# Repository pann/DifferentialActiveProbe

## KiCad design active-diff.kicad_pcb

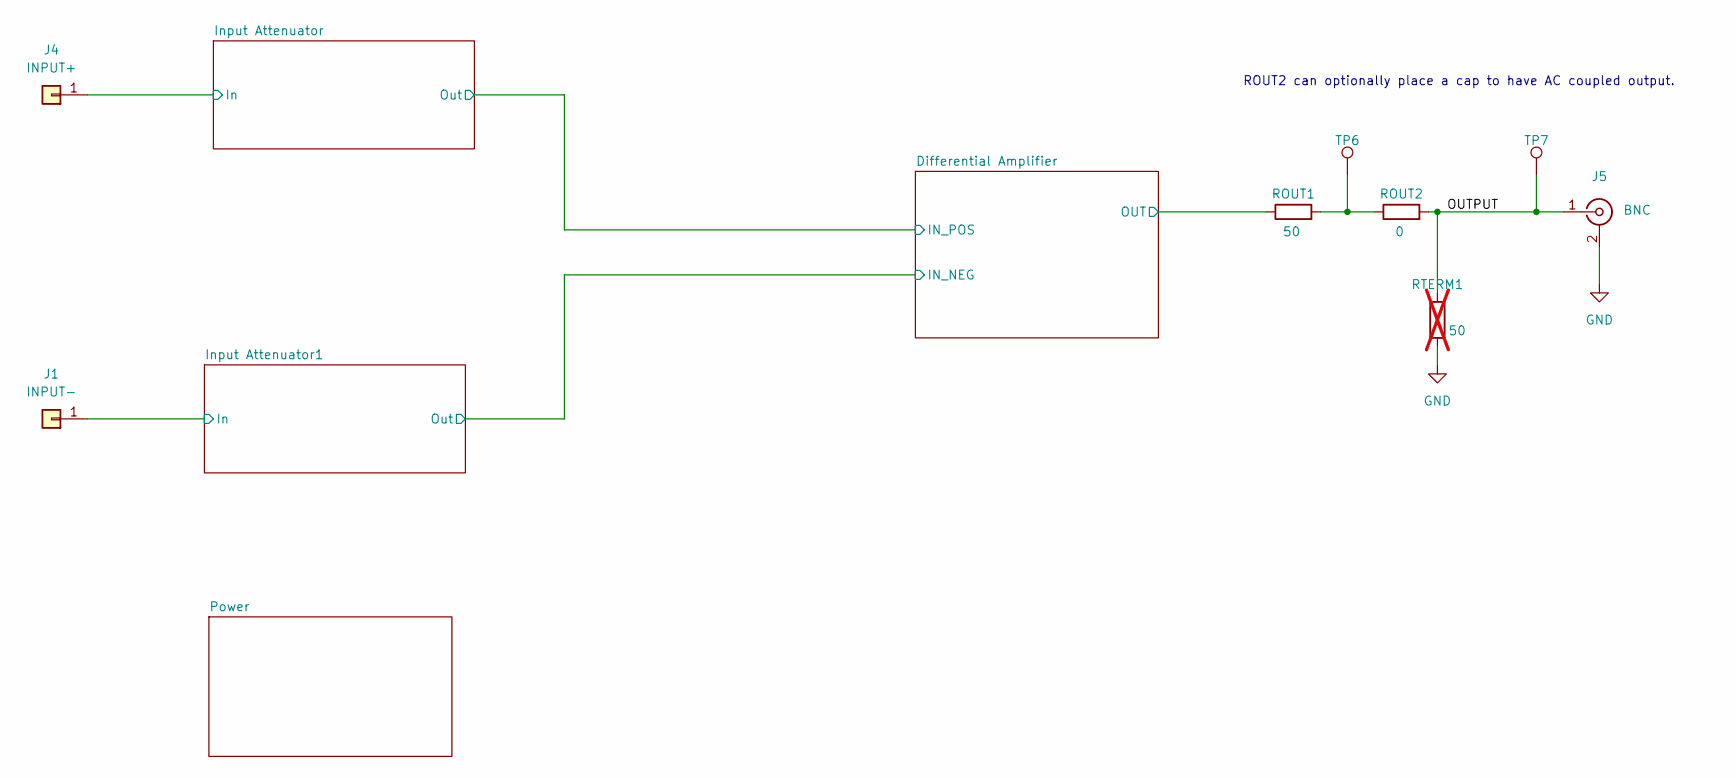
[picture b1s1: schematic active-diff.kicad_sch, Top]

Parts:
J1: INPUT-; TestPoint_Pad_2.5x2.5mm
J4: INPUT+; TestPoint_Pad_2.5x2.5mm
J5: BNC; BNC_Amphenol_B6252HB-NPP3G-50_Horizontal
ROUT1: 50; R_0402_1005Metric_Pad0.72x0.64mm_HandSolder; JLCPCB# C227387
ROUT2: 0; R_0402_1005Metric_Pad0.72x0.64mm_HandSolder; JLCPCB# C17168
RTERM1: 50; R_0402_1005Metric_Pad0.72x0.64mm_HandSolder; not fitted
TP6, TP7: TP; TestPoint_Pad_D1.0mm

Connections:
/Differential Amplifier/OUT: ROUT1.1; also elsewhere on the board
/Input Attenuator1/In: J1.1; also elsewhere on the board
/Input Attenuator/In: J4.1; also elsewhere on the board
/OUTPUT: J5.1 (In), ROUT2.2, RTERM1.1, TP7.1
GND: J5.2 (Ext), RTERM1.2; also elsewhere on the board
unnamed: ROUT1.2, ROUT2.1, TP6.1

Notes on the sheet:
ROUT2 can optionally place a cap to have AC coupled output.

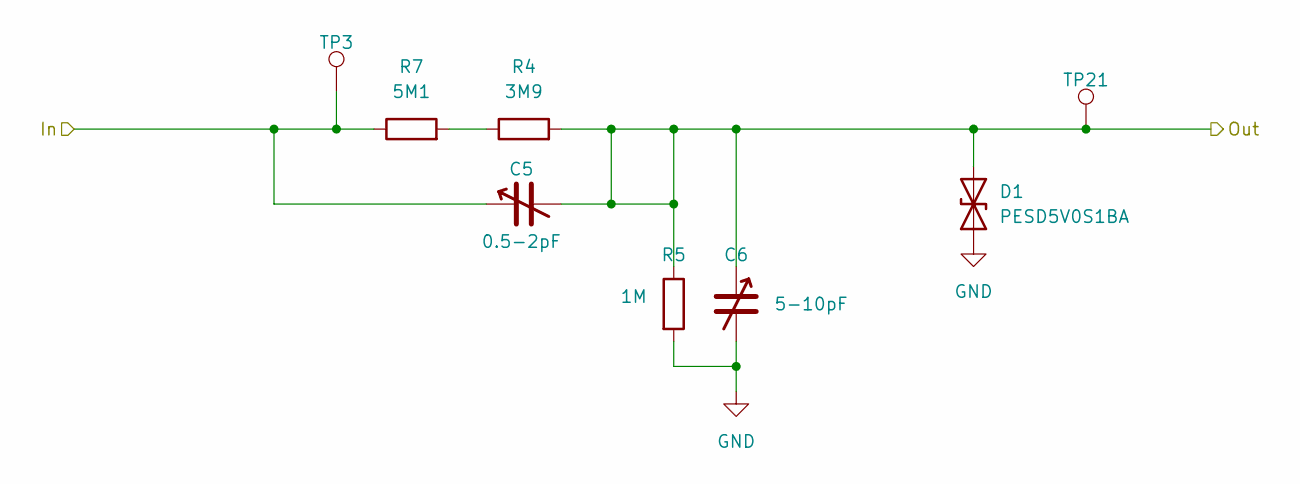
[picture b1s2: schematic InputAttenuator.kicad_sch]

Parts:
C5: 0.5-2pF; C_Trimmer_Murata_TZC3; JLCPCB# C22468120
C6: 5-10pF; C_Trimmer_Murata_TZC3; JLCPCB# C22468120
D1: PESD5V0S1BA; D_SOD-323_HandSoldering; JLCPCB# C2827694
R4: 3M9; R_0603_1608Metric_Pad0.98x0.95mm_HandSolder; Tolerance 0.1%; JLCPCB# C423039
R5: 1M; R_0603_1608Metric_Pad0.98x0.95mm_HandSolder; Tolerance 0.1%; JLCPCB# C4165581
R7: 5M1; R_0603_1608Metric_Pad0.98x0.95mm_HandSolder; Tolerance 0.1%; JLCPCB# C13320
TP3, TP21: TP; TestPoint_Pad_D1.0mm

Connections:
/Differential Amplifier/IN_POS: C5.2, C6.1, D1.2 (A2), R4.2, R5.1, TP21.1; also elsewhere on the board
/Input Attenuator/In: C5.1, R7.1, TP3.1; also elsewhere on the board
GND: C6.2, D1.1 (A1), R5.2; also elsewhere on the board
unnamed: R4.1, R7.2

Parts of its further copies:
C1: 0.5-2pF; C_Trimmer_Murata_TZC3; JLCPCB# C22468120
C2: 5-10pF; C_Trimmer_Murata_TZC3; JLCPCB# C22468120
D2: PESD5V0S1BA; D_SOD-323_HandSoldering; JLCPCB# C2827694
R1: 3M9; R_0603_1608Metric_Pad0.98x0.95mm_HandSolder; Tolerance 0.1%; JLCPCB# C423039
R2: 1M; R_0603_1608Metric_Pad0.98x0.95mm_HandSolder; Tolerance 0.1%; JLCPCB# C4165581
R16: 5M1; R_0603_1608Metric_Pad0.98x0.95mm_HandSolder; Tolerance 0.1%; JLCPCB# C13320
TP1, TP22: TP; TestPoint_Pad_D1.0mm

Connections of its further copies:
/Differential Amplifier/IN_NEG: C1.2, C2.1, D2.2 (A2), R1.2, R2.1, TP22.1; also elsewhere on the board
/Input Attenuator1/In: C1.1, R16.1, TP1.1; also elsewhere on the board
GND: C2.2, D2.1 (A1), R2.2; also elsewhere on the board
unnamed: R1.1, R16.2

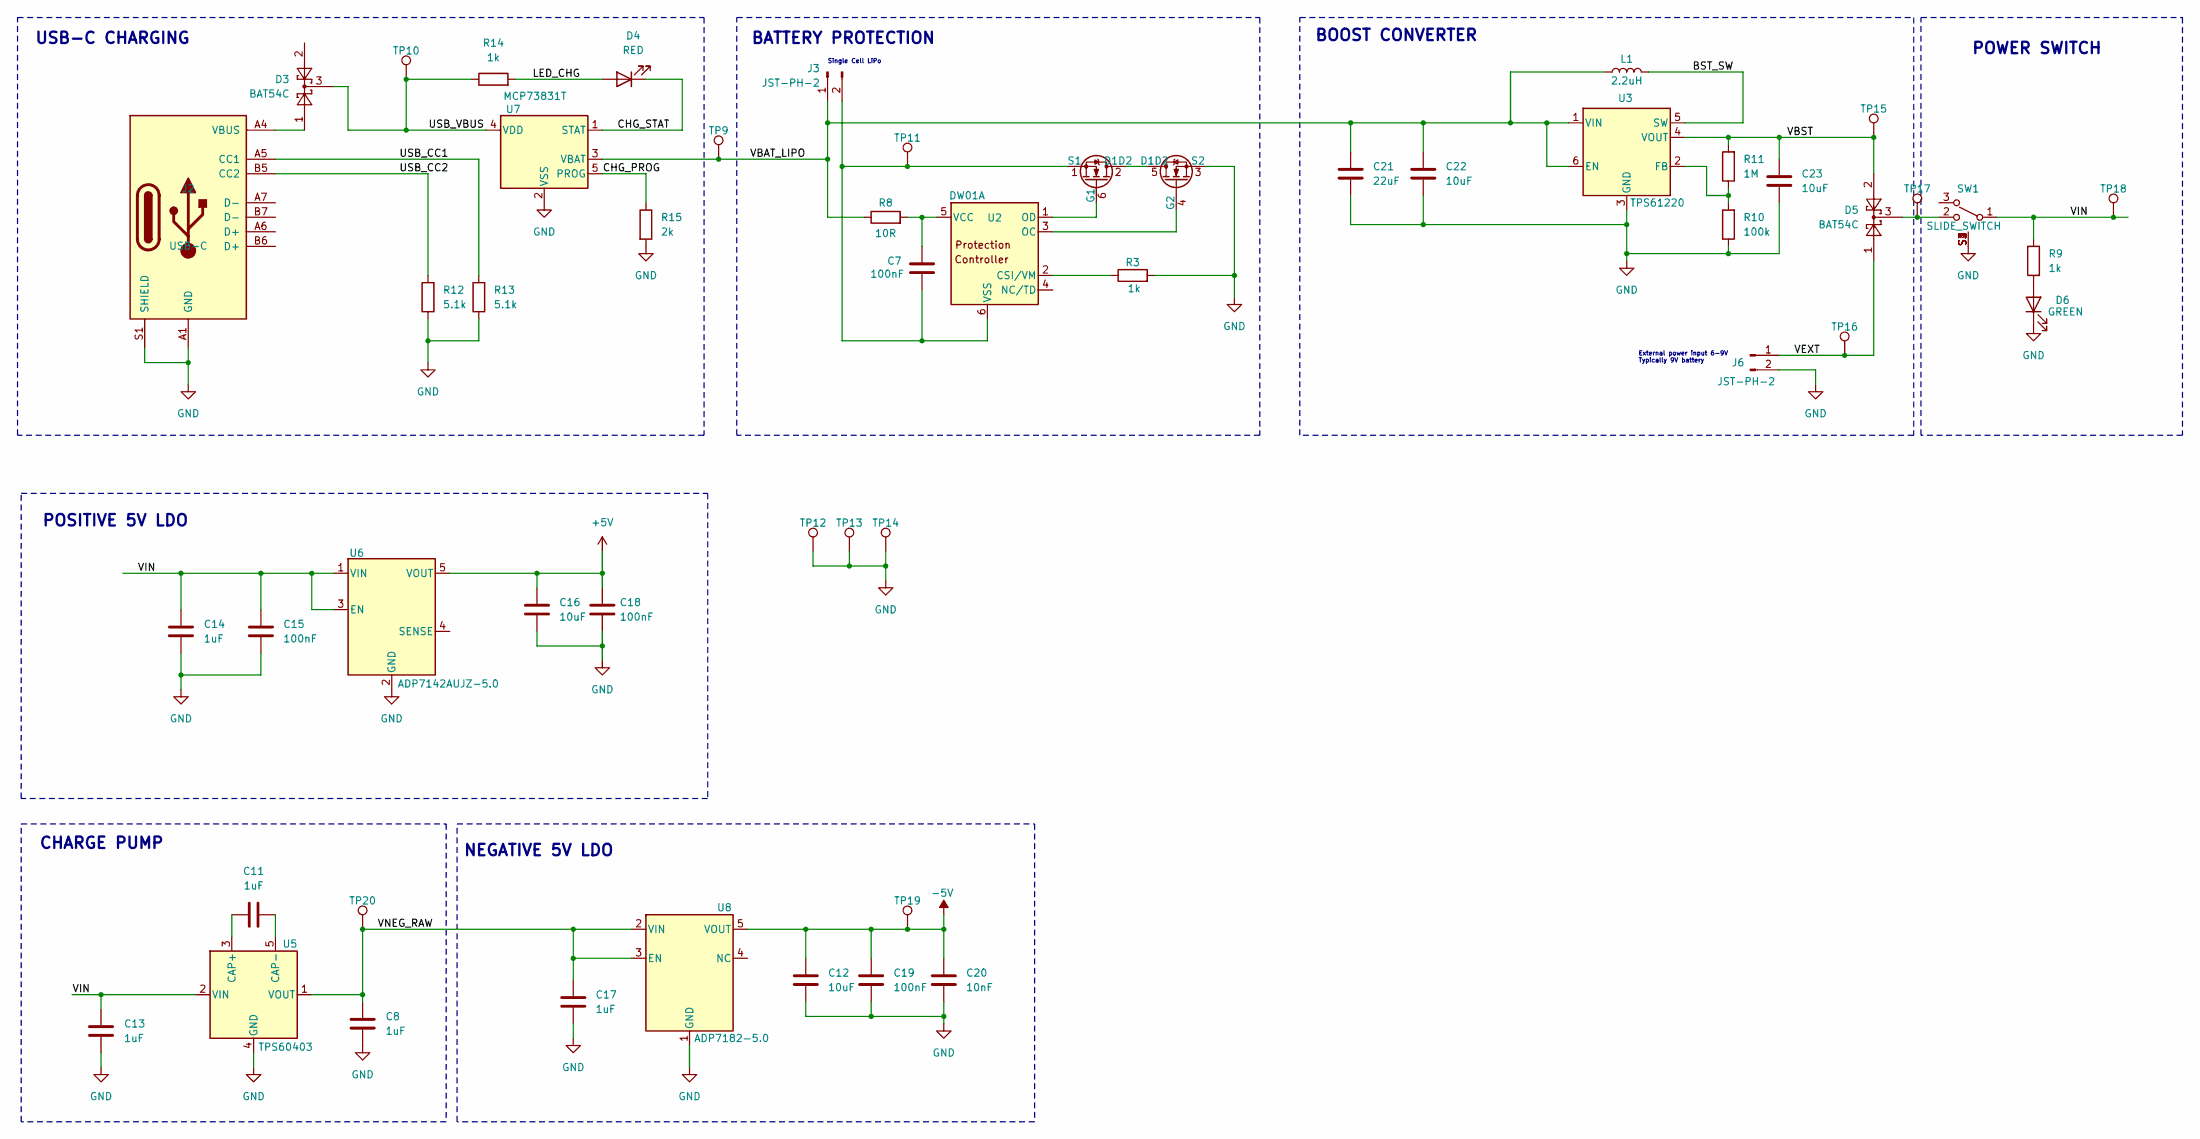
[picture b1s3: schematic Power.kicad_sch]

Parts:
C7: 100nF; C_0402_1005Metric_Pad0.74x0.62mm_HandSolder; Voltage 16V; JLCPCB# C60474
C8, C11, C13, C14, C17: 1uF; C_0603_1608Metric; Voltage 16V; JLCPCB# C59782
C12, C16, C22, C23: 10uF; C_0603_1608Metric_Pad1.08x0.95mm_HandSolder; Voltage 16V; JLCPCB# C237435
C15, C18, C19: 100nF; C_0402_1005Metric_Pad0.74x0.62mm_HandSolder; Voltage 10V; JLCPCB# C60474
C20: 10nF; C_0402_1005Metric_Pad0.74x0.62mm_HandSolder; Voltage 10V; JLCPCB# C15195
C21: 22uF; C_0805_2012Metric_Pad1.18x1.45mm_HandSolder; Voltage 16V; JLCPCB# C296720
D3, D5: BAT54C; SOT-23; MPN BAT54C; JLCPCB# C2135
D4: RED; LED_0805_2012Metric; JLCPCB# C2295
D6: GREEN; LED_0805_2012Metric; JLCPCB# C2297
J2: USB-C; USB_C_Receptacle_HRO_TYPE-C-31-M-12; MPN TYPE-C-31-M-12; JLCPCB# C165948
J3, J6: JST-PH-2; JST_PH_S2B-PH-K_1x02_P2.00mm_Horizontal; MPN S2B-PH-K-S; JLCPCB# C173752
L1: 2.2uH; L_Changjiang_FTC303010D; MPN VLS3012ET-2R2M; JLCPCB# C136233
Q1: FS8205A; TSOT-23-6; MPN FS8205A; JLCPCB# C2830320
R3: 1k; R_0402_1005Metric; Tolerance 1%; JLCPCB# C11702
R8: 10R; R_0402_1005Metric_Pad0.72x0.64mm_HandSolder; Tolerance 1%; JLCPCB# C25077
R9, R14: 1k; R_0402_1005Metric_Pad0.72x0.64mm_HandSolder; Tolerance 5%; JLCPCB# C11702
R10: 100k; R_0402_1005Metric_Pad0.72x0.64mm_HandSolder; Tolerance 1%; JLCPCB# C25741
R11: 1M; R_0402_1005Metric_Pad0.72x0.64mm_HandSolder; Tolerance 1%; JLCPCB# C26083
R12, R13: 5.1k; R_0402_1005Metric_Pad0.72x0.64mm_HandSolder; Tolerance 5%; JLCPCB# C25905
R15: 2k; R_0402_1005Metric_Pad0.72x0.64mm_HandSolder; Tolerance 5%; JLCPCB# C4109
SW1: SLIDE_SWITCH; SW_PCM12SMTR; MPN PCM12SMTR; JLCPCB# C221841
TP9, TP10, TP11, TP12, TP13, TP14, TP15, TP16, TP17, TP18, TP19, TP20: TP; TestPoint_Pad_D1.0mm
U2: DW01A; SOT-23-6; MPN DW01A; JLCPCB# C2927799
U3: TPS61220; SOT-363_SC-70-6; MPN TPS61220DCKR; JLCPCB# C15421
U5: TPS60403; SOT-23-5; MPN TPS60403DBVR; JLCPCB# C11338
U6: ADP7142AUJZ-5.0; TSOT-23-5; MPN ADP7142AUJZ-5.0-R7; JLCPCB# C659367
U7: MCP73831T; SOT-23-5; MPN MCP73831T-2ACI/OT; JLCPCB# C424093
U8: ADP7182-5.0; TSOT-23-5; MPN ADP7182ARDZ-5.0-R7; JLCPCB# C514357

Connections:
+5V: C16.2, C18.2, U6.5 (VOUT); also elsewhere on the board
-5V: C12.2, C19.2, C20.2, TP19.1, U8.5 (VOUT); also elsewhere on the board
/Power/BST_SW: L1.2, U3.5 (SW)
/Power/CHG_PROG: R15.1, U7.5 (PROG)
/Power/CHG_STAT: D4.1 (K), U7.1 (STAT)
/Power/LED_CHG: D4.2 (A), R14.2
/Power/USB_CC1: J2.A5 (CC1), R13.2
/Power/USB_CC2: J2.B5 (CC2), R12.2
/Power/USB_VBUS: D3.3, R14.1, TP10.1, U7.4 (VDD)
/Power/VBAT_LIPO: C21.2, C22.2, J3.1, L1.1, R8.1, TP9.1, U3.1 (VIN), U3.6 (EN), U7.3 (VBAT)
/Power/VBST: C23.2, D5.2, R11.2, TP15.1, U3.4 (VOUT)
/Power/VEXT: D5.1, J6.1, TP16.1
/Power/VIN: C13.2, C14.2, C15.2, R9.2, SW1.1 (A), TP18.1, U5.2 (VIN), U6.1 (VIN), U6.3 (EN)
/Power/VNEG_RAW: C8.2, C17.2, TP20.1, U5.1 (VOUT), U8.2 (VIN), U8.3 (EN)
GND: C8.1, C12.1, C13.1, C14.1, C15.1, C16.1, C17.1, C18.1, C19.1, C20.1, C21.1, C22.1, C23.1, D6.1 (K), J2.A1 (GND), J2.A12 (GND), J2.B1 (GND), J2.B12 (GND), J2.S1 (SHIELD), J6.2, Q1.3 (S2), R3.2, R10.1, R12.1, R13.1, R15.2, SW1.S1, SW1.S2, SW1.S3, SW1.S4, TP12.1, TP13.1, TP14.1, U3.3 (GND), U5.4 (GND), U6.2 (GND), U7.2 (VSS), U8.1 (GND); also elsewhere on the board
unnamed: D3.1, J2.A4 (VBUS), J2.A9 (VBUS), J2.B4 (VBUS), J2.B9 (VBUS)
unnamed: D5.3, SW1.2 (B), TP17.1
unnamed: D6.2 (A), R9.1
unnamed: C7.2, J3.2, Q1.1 (S1), TP11.1, U2.6 (VSS)
unnamed: Q1.2 (D1D2), Q1.5 (D1D2)
unnamed: Q1.6 (G1), U2.1 (OD)
unnamed: Q1.4 (G2), U2.3 (OC)
unnamed: R3.1, U2.2 (CSI/VM)
unnamed: C7.1, R8.2, U2.5 (VCC)
unnamed: R10.2, R11.1, U3.2 (FB)
unnamed: C11.2, U5.3 (CAP+)
unnamed: C11.1, U5.5 (CAP-)

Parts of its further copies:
TP1: TP; TestPoint_Pad_D1.0mm

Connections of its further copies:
/Input Attenuator1/In: TP1.1; also elsewhere on the board

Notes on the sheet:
USB-C CHARGING
POSITIVE 5V LDO
CHARGE PUMP
POWER SWITCH
BATTERY PROTECTION
BOOST CONVERTER
NEGATIVE 5V LDO
Single Cell LiPo
External power input 6-9V Typically 9V battery

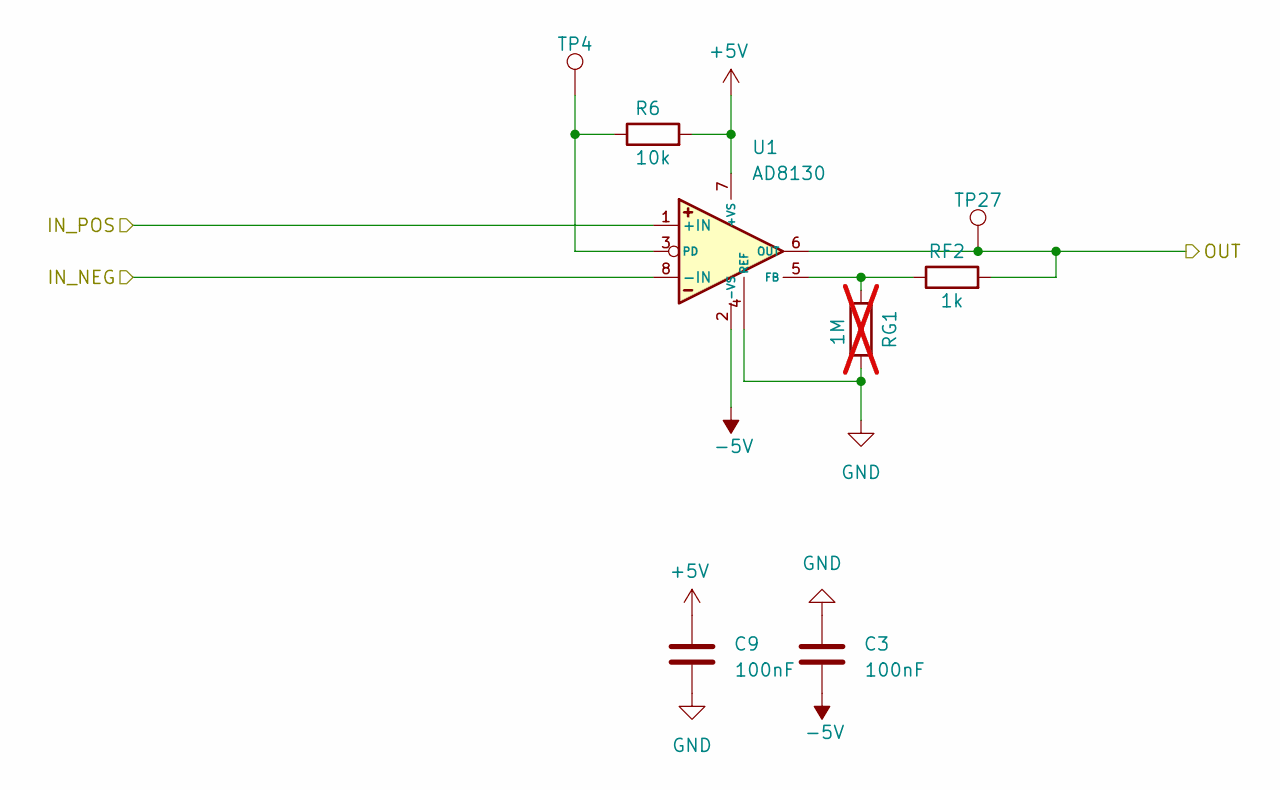
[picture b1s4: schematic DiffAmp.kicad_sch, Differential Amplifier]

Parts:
C3, C9: 100nF; C_0402_1005Metric_Pad0.74x0.62mm_HandSolder; Voltage 16V; JLCPCB# C60474
R6: 10k; R_0402_1005Metric_Pad0.72x0.64mm_HandSolder; Tolerance 0.1%; JLCPCB# C25744
RF2: 1k; R_0402_1005Metric_Pad0.72x0.64mm_HandSolder; Tolerance 0.1%; JLCPCB# C11702
RG1: 1M; R_0402_1005Metric_Pad0.72x0.64mm_HandSolder; Tolerance 0.1%; not fitted
TP4, TP27: TP; TestPoint_Pad_D1.0mm
U1: AD8130; SOIC-8_3.9x4.9mm_P1.27mm; JLCPCB# C41661

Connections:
+5V: C9.1, R6.2, U1.7 (+VS); also elsewhere on the board
-5V: C3.2, U1.2 (-VS); also elsewhere on the board
/Differential Amplifier/IN_NEG: U1.8 (-IN); also elsewhere on the board
/Differential Amplifier/IN_POS: U1.1 (+IN); also elsewhere on the board
/Differential Amplifier/OUT: RF2.2, TP27.1, U1.6 (OUT); also elsewhere on the board
GND: C3.1, C9.2, RG1.2, U1.4 (REF); also elsewhere on the board
unnamed: RF2.1, RG1.1, U1.5 (FB)
unnamed: R6.1, TP4.1, U1.3 (PD)

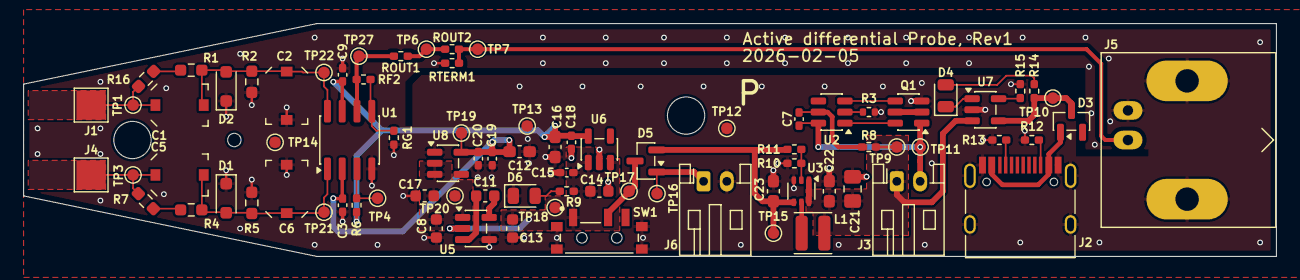
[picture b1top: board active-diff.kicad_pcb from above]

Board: 2 copper layers, 107.6 x 20.0 mm, 84 parts (0 on the bottom side), 38 nets.

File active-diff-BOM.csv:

"Designator","Qty","Comment","Footprint","JLCPCB Part#"
"J5","1","BNC","Connector_Coaxial:BNC_Amphenol_B6252HB-NPP3G-50_Horizontal",""
"D3,D5","2","BAT54C","Package_TO_SOT_SMD:SOT-23","C2135"
"D4","1","RED","LED_SMD:LED_0805_2012Metric","C2295"
"D6","1","GREEN","LED_SMD:LED_0805_2012Metric","C2297"
"R15","1","2k","Resistor_SMD:R_0402_1005Metric_Pad0.72x0.64mm_HandSolder","C4109"
"U5","1","TPS60403","Package_TO_SOT_SMD:SOT-23-5","C11338"
"R3","1","1k","Resistor_SMD:R_0402_1005Metric","C11702"
"R9,R14,RF2","3","1k","Resistor_SMD:R_0402_1005Metric_Pad0.72x0.64mm_HandSolder","C11702"
"R7,R16","2","5M1","Resistor_SMD:R_0603_1608Metric_Pad0.98x0.95mm_HandSolder","C13320"
"C20","1","10nF","Capacitor_SMD:C_0402_1005Metric_Pad0.74x0.62mm_HandSolder","C15195"
"U3","1","TPS61220","Package_TO_SOT_SMD:SOT-363_SC-70-6","C15421"
"ROUT2","1","0","Resistor_SMD:R_0402_1005Metric_Pad0.72x0.64mm_HandSolder","C17168"
"R8","1","10R","Resistor_SMD:R_0402_1005Metric_Pad0.72x0.64mm_HandSolder","C25077"
"R10","1","100k","Resistor_SMD:R_0402_1005Metric_Pad0.72x0.64mm_HandSolder","C25741"
"R6","1","10k","Resistor_SMD:R_0402_1005Metric_Pad0.72x0.64mm_HandSolder","C25744"
"R12,R13","2","5.1k","Resistor_SMD:R_0402_1005Metric_Pad0.72x0.64mm_HandSolder","C25905 "
"R11","1","1M","Resistor_SMD:R_0402_1005Metric_Pad0.72x0.64mm_HandSolder","C26083"
"U1","1","AD8130","Package_SO:SOIC-8_3.9x4.9mm_P1.27mm","C41661"
"C8,C11,C13,C14,C17","5","1uF","Capacitor_SMD:C_0603_1608Metric","C59782"
"C3,C7,C9,C15,C18,C19","6","100nF","Capacitor_SMD:C_0402_1005Metric_Pad0.74x0.62mm_HandSolder","C60474"
"L1","1","2.2uH","Inductor_SMD:L_Changjiang_FTC303010D","C136233"
"J2","1","USB-C","Connector_USB:USB_C_Receptacle_HRO_TYPE-C-31-M-12","C165948"
"J3,J6","2","JST-PH-2","Connector_JST:JST_PH_S2B-PH-K_1x02_P2.00mm_Horizontal","C173752 "
"SW1","1","SLIDE_SWITCH","ProjectLib:SW_PCM12SMTR","C221841"
"ROUT1","1","50","Resistor_SMD:R_0402_1005Metric_Pad0.72x0.64mm_HandSolder","C227387"
"C12,C16,C22,C23","4","10uF","Capacitor_SMD:C_0603_1608Metric_Pad1.08x0.95mm_HandSolder","C237435"
"C21","1","22uF","Capacitor_SMD:C_0805_2012Metric_Pad1.18x1.45mm_HandSolder","C296720"
"R1,R4","2","3M9","Resistor_SMD:R_0603_1608Metric_Pad0.98x0.95mm_HandSolder","C423039"
"U7","1","MCP73831T","Package_TO_SOT_SMD:SOT-23-5","C424093"
"U8","1","ADP7182-5.0","Package_TO_SOT_SMD:TSOT-23-5","C514357"
"U6","1","ADP7142AUJZ-5.0","Package_TO_SOT_SMD:TSOT-23-5","C659367"
"D1,D2","2","PESD5V0S1BA","Diode_SMD:D_SOD-323_HandSoldering","C2827694"
"Q1","1","FS8205A","Package_TO_SOT_SMD:TSOT-23-6","C2830320"
"U2","1","DW01A","Package_TO_SOT_SMD:SOT-23-6","C2927799"
"R2,R5","2","1M","Resistor_SMD:R_0603_1608Metric_Pad0.98x0.95mm_HandSolder","C4165581"
"C1,C5","2","0.5-2pF","Capacitor_SMD:C_Trimmer_Murata_TZC3","C22468120"
"C2,C6","2","5-10pF","Capacitor_SMD:C_Trimmer_Murata_TZC3","C22468120"

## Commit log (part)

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2026-02-04 DRC completed. Need to add some 3D models.
2026-02-06 R1 sent to JLCPCB
